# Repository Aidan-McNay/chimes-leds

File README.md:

# chimes-leds
A system for controlling McGraw Tower's clock face LEDs

## Documentation

Documentation for our system is located [here](https://aidan-mcnay.github.io/chimes-leds/)

Our documentation is built using Sphinx, and is
formatted as [reStructured Text](https://www.sphinx-doc.org/en/master/usage/restructuredtext/basics.html).
To build the documentation locally, first install Sphinx,
as well as our additional Sphinx modules:

```bash
pip install sphinx sphinx_rtd_theme sphinxcontrib-youtube
```

Then, you can build the output files in a `build`
directory with Sphinx, with the top-level HTML
located at `build/index.html`

```bash
sphinx-build docs build
```

This process is automated to update the Github page
on a push

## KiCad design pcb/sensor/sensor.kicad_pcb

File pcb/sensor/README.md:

# sensor

The PCB files for the control board at the playing stand level

## GPIO Mapping

**Microphone**:
 - **26**: Microphone ADC input

**Ambient Light**:
 - **21**: SCL
 - **20**: SDA
 - **19**: Interrupt (if desired)

**CAN connections**:
 - **16**: CAN TX
 - **17**: CAN RX
 - **22**: CAN Enable (active low)

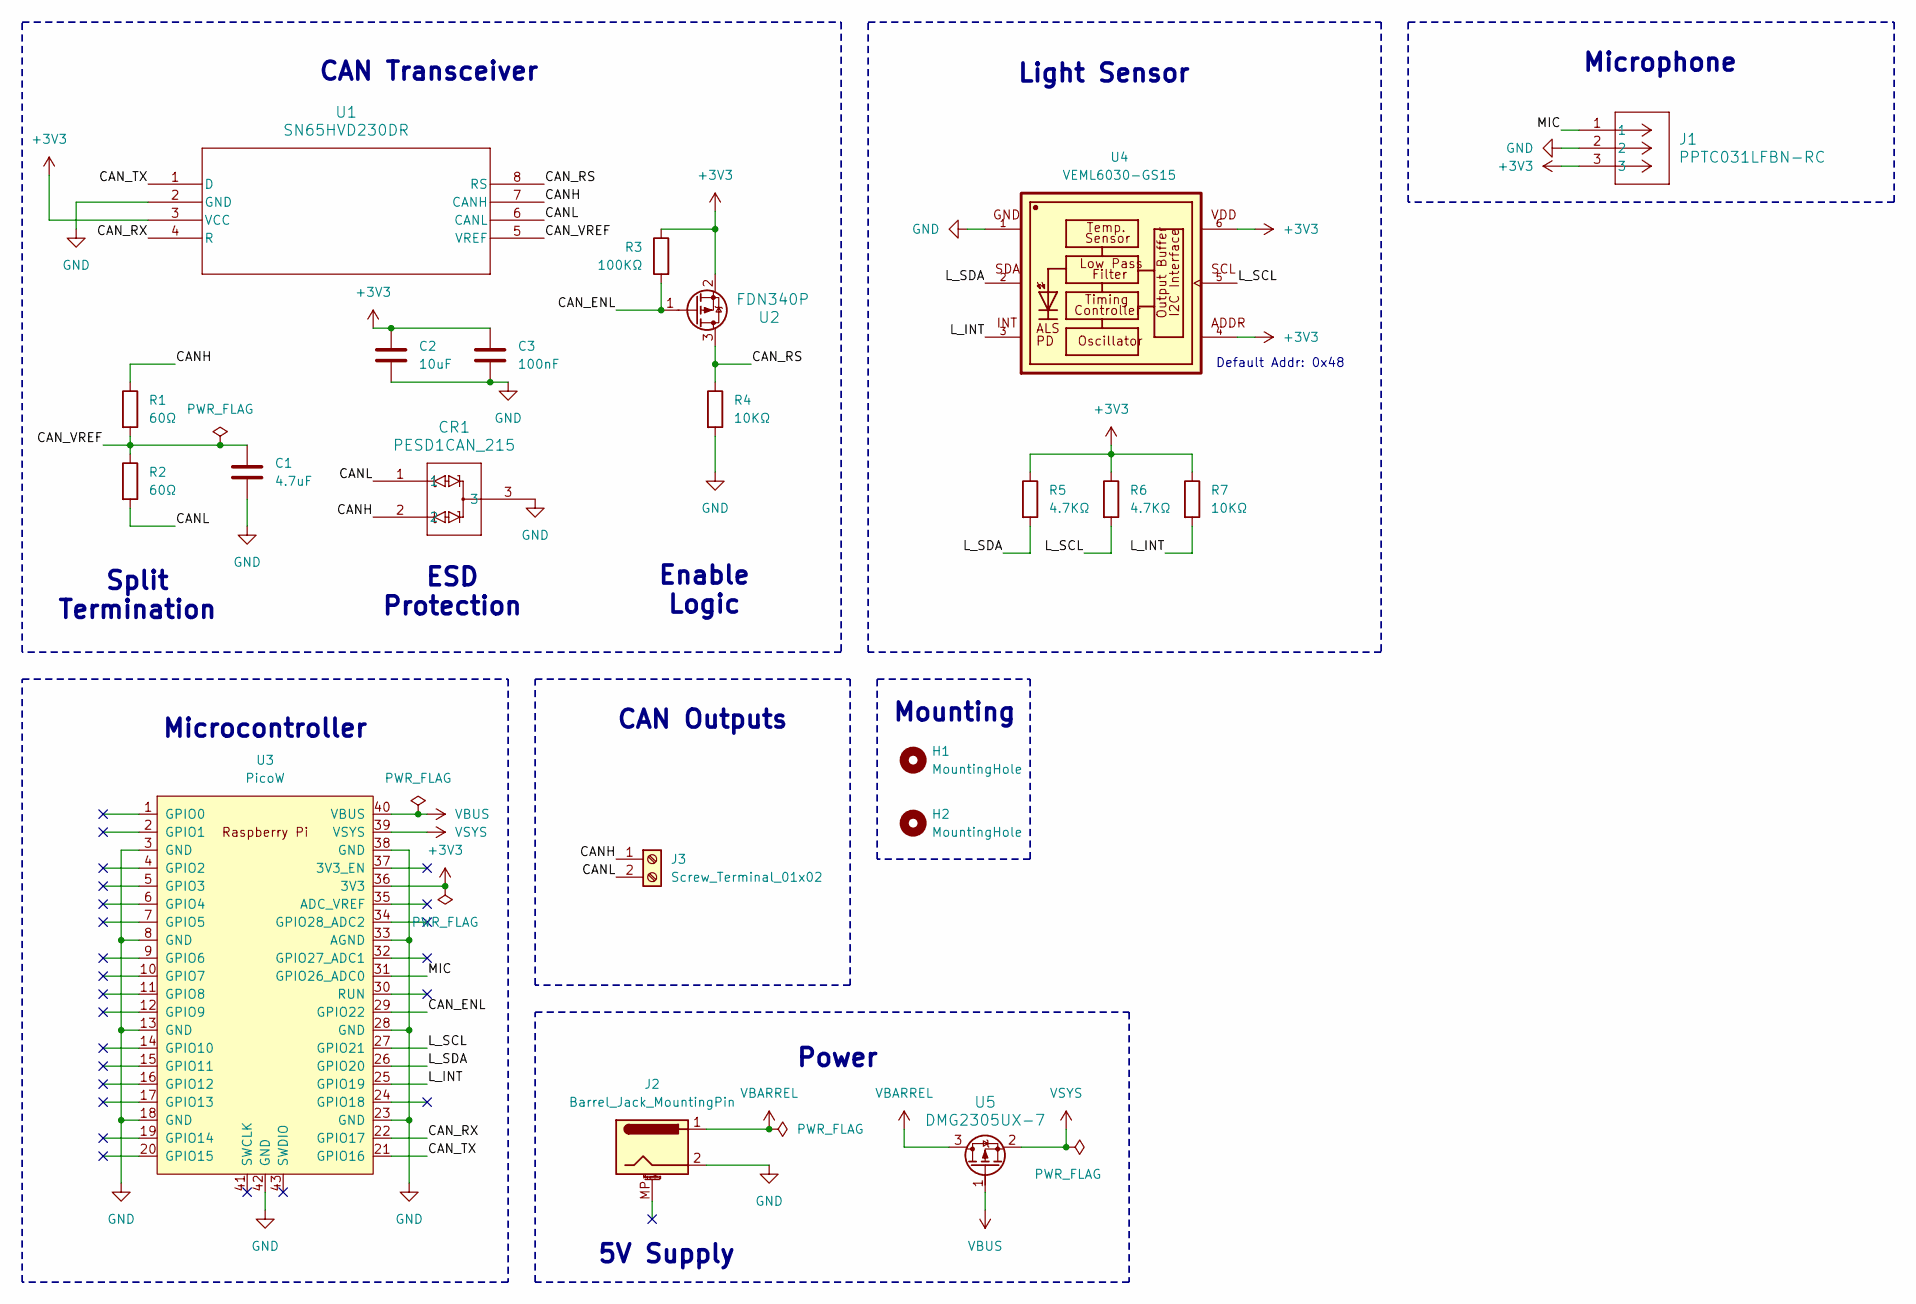
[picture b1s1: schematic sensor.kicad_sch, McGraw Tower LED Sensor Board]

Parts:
C1: 4.7uF; C_0603_1608Metric
C2: 10uF; C_0603_1608Metric
C3: 100nF; C_0603_1608Metric
CR1: PESD1CAN_215; SOT23_PESD1_NEX
H1, H2: MountingHole; MountingHole_3.2mm_M3_DIN965_Pad
J1: PPTC031LFBN-RC; CONN_PPTC031_SUL
J2: Barrel_Jack_MountingPin; BarrelJack_CUI_PJ-102AH_Horizontal
J3: Screw_Terminal_01x02; TerminalBlock_Phoenix_PT-1,5-2-5.0-H_1x02_P5.00mm_Horizontal
R1, R2: 60Ω; R_1206_3216Metric
R3: 100KΩ; R_0603_1608Metric
R4, R7: 10KΩ; R_0603_1608Metric
R5, R6: 4.7KΩ; R_0603_1608Metric
U1: SN65HVD230DR; D8
U2: FDN340P; SOT-23_ONS
U3: PicoW; RPi_PicoW_SMD_TH
U4: VEML6030-GS15; VISHAY_VEML6030_2X2X0.87
U5: DMG2305UX-7; SOT-23_DIO

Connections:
+3V3: C2.1, C3.1, J1.3, R3.1, R5.1, R6.1, R7.1, U1.3 (VCC), U2.2, U3.36 (3V3), U4.4, U4.6
/CANH: CR1.2, J3.1, R1.1, U1.7 (CANH)
/CANL: CR1.1, J3.2, R2.2, U1.6 (CANL)
/CAN_ENL: R3.2, U2.1, U3.29 (GPIO22)
/CAN_RS: R4.1, U1.8 (RS), U2.3
/CAN_RX: U1.4 (R), U3.22 (GPIO17)
/CAN_TX: U1.1 (D), U3.21 (GPIO16)
/CAN_VREF: C1.1, R1.2, R2.1, U1.5 (VREF)
/L_INT: R7.2, U3.25 (GPIO19), U4.3
/L_SCL: R6.2, U3.27 (GPIO21), U4.5
/L_SDA: R5.2, U3.26 (GPIO20), U4.2
/MIC: J1.1, U3.31 (GPIO26_ADC0)
GND: C1.2, C2.2, C3.2, CR1.3, J1.2, J2.2, R4.2, U1.2 (GND), U3.3 (GND), U3.8 (GND), U3.13 (GND), U3.18 (GND), U3.23 (GND), U3.28 (GND), U3.33 (AGND), U3.38 (GND), U3.42 (GND), U4.1
VBARREL: J2.1, U5.3
VBUS: U3.40 (VBUS), U5.1
VSYS: U3.39 (VSYS), U5.2

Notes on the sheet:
Microphone
CAN Outputs
Microcontroller
CAN Transceiver
Enable Logic
Power
5V Supply
Light Sensor
Mounting
ESD Protection
Split Termination
Default Addr: 0x48

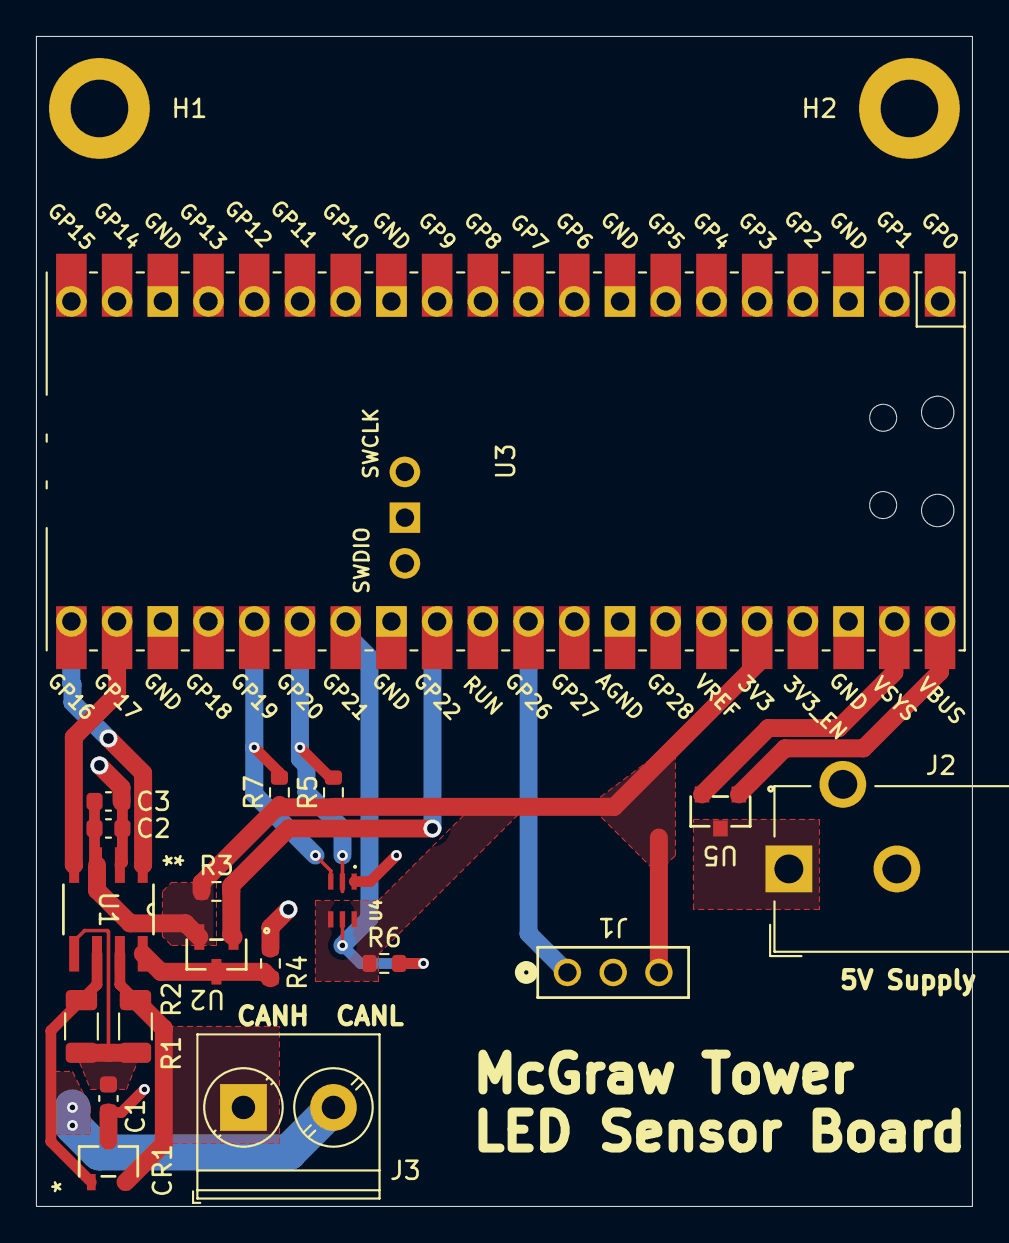
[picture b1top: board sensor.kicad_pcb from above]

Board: 2 copper layers, 52.0 x 65.0 mm, 21 parts (0 on the bottom side), 16 nets.

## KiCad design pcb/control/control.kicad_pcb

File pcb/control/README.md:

# control

The PCB files for the control board at the playing stand level

## GPIO Mapping

**System Configuration**:
 - **4**: System enable (whether to be on)
 - **5**: WiFi enable (whether to use WiFi configs)

**User Mode**:
 - **7**: "Light" mode (based on ambient light, set as pull-down)
 - **8**: "Music" mode (pulse with music, set as pull-down)
 - **9**: "On" mode (always on, set as pull-down)

**Color Potentiometer Inputs**
 - **28**: Red Potentiometer
 - **27**: Green Potentiometer
 - **26**: Blue Potentiometer

**Status LEDs**:
 - **10**: "On" LED (high when enabled)
 - **11**: Red LED (PWM for current color)
 - **12**: Green LED (PWM for current color)
 - **14**: Blue LED (PWM for current color)
 - **15**: WiFi LED (indicate where configs are from)

**Communication LEDs** *(whether we're communicating with a board)*:
 - **3**: Sensor Board
 - **21**: North Face
 - **20**: South Face
 - **19**: East Face
 - **18**: West Face

**CAN connections**:
 - **16**: CAN TX
 - **17**: CAN RX
 - **22**: CAN Enable (active low)

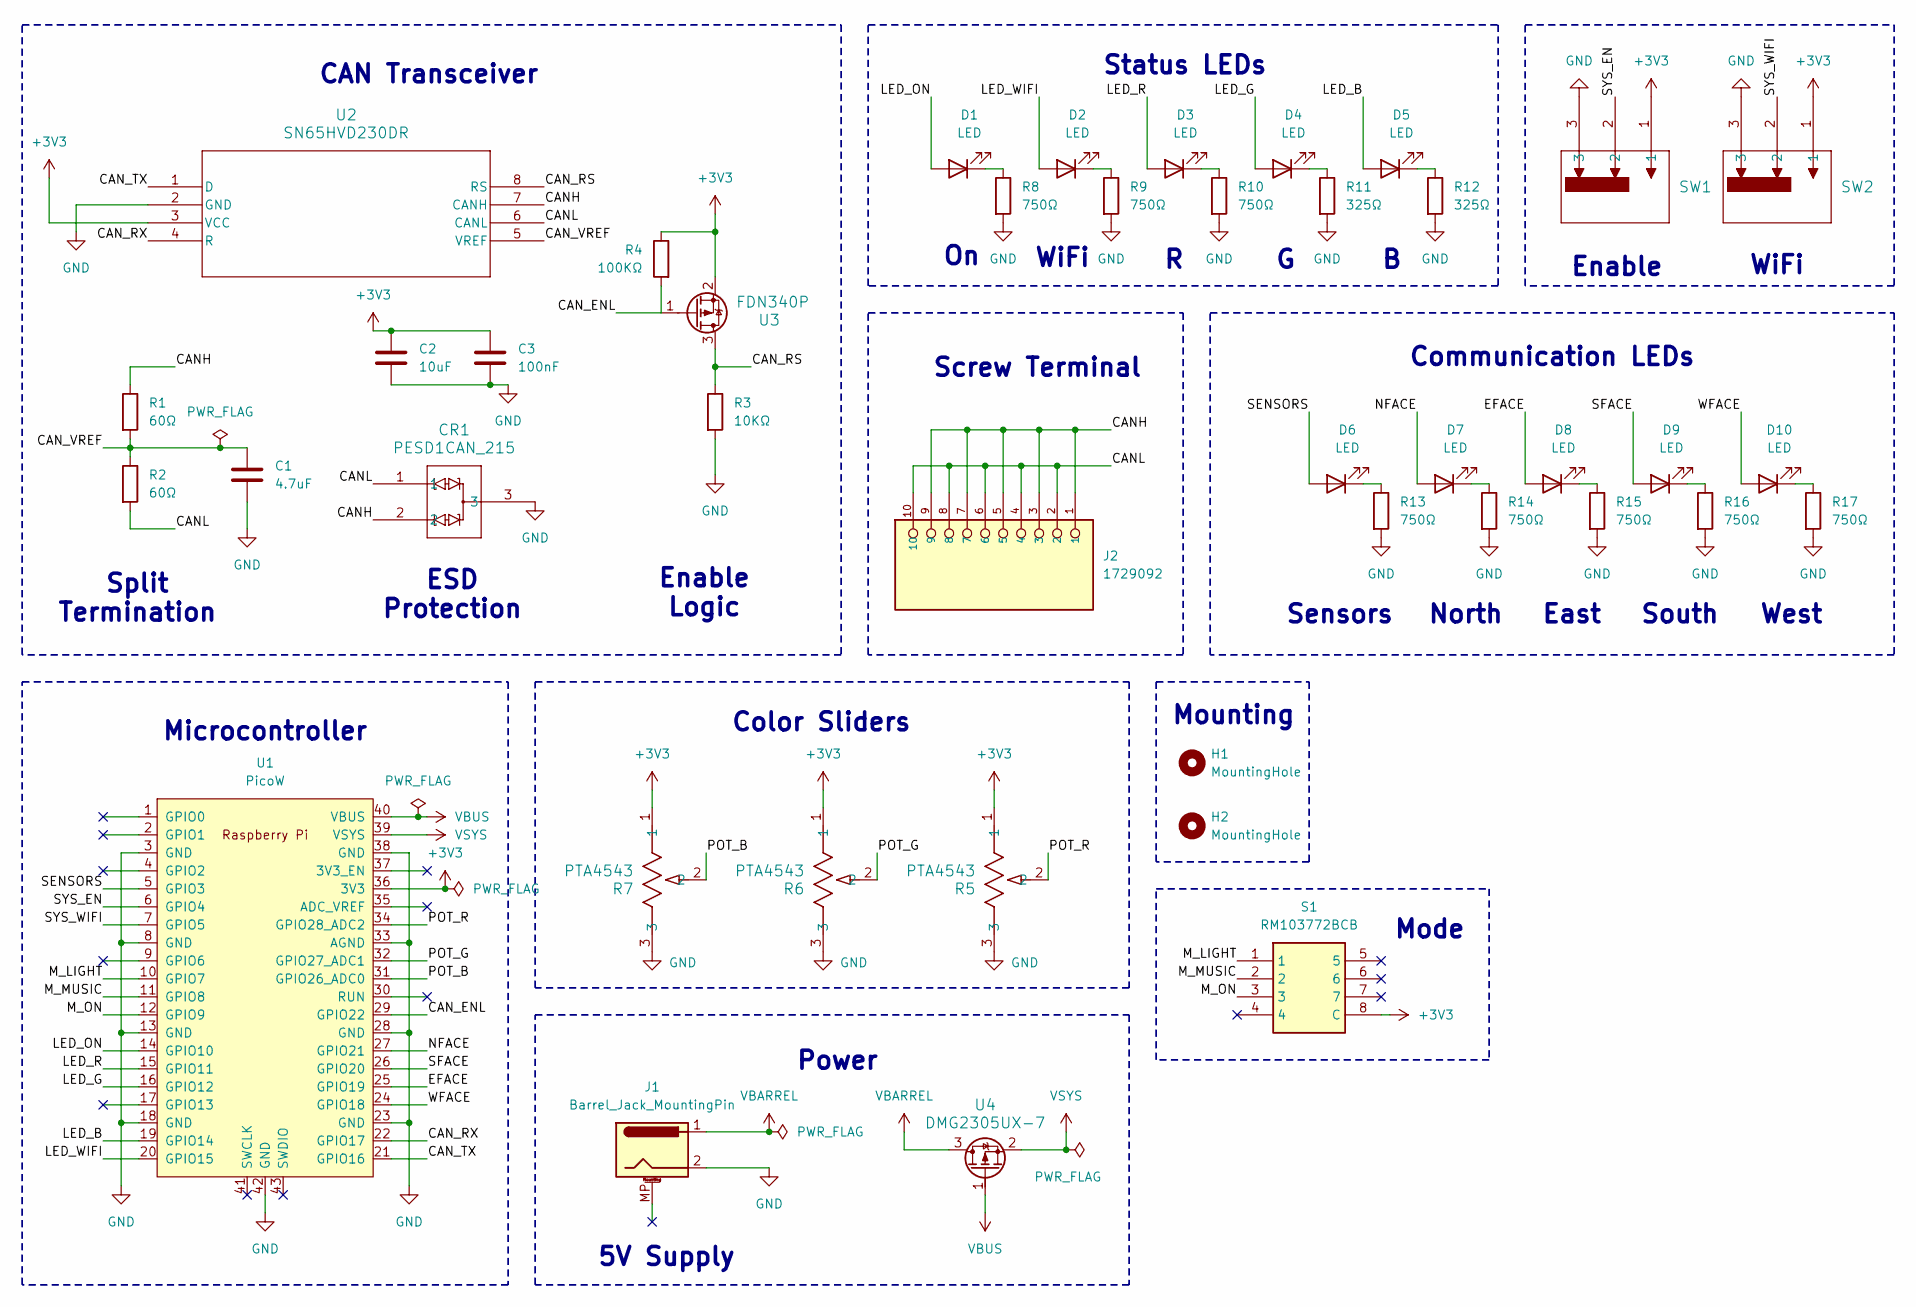
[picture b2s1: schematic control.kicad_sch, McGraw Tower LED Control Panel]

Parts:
C1: 4.7uF; C_0603_1608Metric
C2: 10uF; C_0603_1608Metric
C3: 100nF; C_0603_1608Metric
CR1: PESD1CAN_215; SOT23_PESD1_NEX
D1, D2, D3, D4, D5, D6, D7, D8, D9, D10: LED; LED_0603_1608Metric
H1, H2: MountingHole; MountingHole_3.2mm_M3_DIN965_Pad
J1: Barrel_Jack_MountingPin; BarrelJack_CUI_PJ-102AH_Horizontal
J2: 1729092; PHOENIX_1729092; DigiKey_Part_Number 277-1244-ND
R1, R2: 60Ω; R_1206_3216Metric
R3: 10KΩ; R_0603_1608Metric
R4: 100KΩ; R_0603_1608Metric
R5, R6, R7: PTA4543; POT_PTA4543
R8, R9, R10, R13, R14, R15, R16, R17: 750Ω; R_1206_3216Metric
R11, R12: 325Ω; R_0603_1608Metric
S1: RM103772BCB; Mouser Part Number 611-RM103772BCB
SW1, SW2: OS102011MS2QN1; SPDT_OS102011_CNK
U1: PicoW; RPi_PicoW_SMD_TH
U2: SN65HVD230DR; D8
U3: FDN340P; SOT-23_ONS
U4: DMG2305UX-7; SOT-23_DIO

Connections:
+3V3: C2.1, C3.1, R4.1, R5.1, R6.1, R7.1, S1.8 (C), SW1.1, SW2.1, U1.36 (3V3), U2.3 (VCC), U3.2
/CANH: CR1.2, J2.1, J2.3, J2.5, J2.7, J2.9, R1.1, U2.7 (CANH)
/CANL: CR1.1, J2.2, J2.4, J2.6, J2.8, J2.10, R2.2, U2.6 (CANL)
/CAN_ENL: R4.2, U1.29 (GPIO22), U3.1
/CAN_RS: R3.1, U2.8 (RS), U3.3
/CAN_RX: U1.22 (GPIO17), U2.4 (R)
/CAN_TX: U1.21 (GPIO16), U2.1 (D)
/CAN_VREF: C1.1, R1.2, R2.1, U2.5 (VREF)
/EFACE: D8.2 (A), U1.25 (GPIO19)
/LED_B: D5.2 (A), U1.19 (GPIO14)
/LED_G: D4.2 (A), U1.16 (GPIO12)
/LED_ON: D1.2 (A), U1.14 (GPIO10)
/LED_R: D3.2 (A), U1.15 (GPIO11)
/LED_WIFI: D2.2 (A), U1.20 (GPIO15)
/M_LIGHT: S1.1, U1.10 (GPIO7)
/M_MUSIC: S1.2, U1.11 (GPIO8)
/M_ON: S1.3, U1.12 (GPIO9)
/NFACE: D7.2 (A), U1.27 (GPIO21)
/POT_B: R7.2, U1.31 (GPIO26_ADC0)
/POT_G: R6.2, U1.32 (GPIO27_ADC1)
/POT_R: R5.2, U1.34 (GPIO28_ADC2)
/SENSORS: D6.2 (A), U1.5 (GPIO3)
/SFACE: D9.2 (A), U1.26 (GPIO20)
/SYS_EN: SW1.2, U1.6 (GPIO4)
/SYS_WIFI: SW2.2, U1.7 (GPIO5)
/WFACE: D10.2 (A), U1.24 (GPIO18)
GND: C1.2, C2.2, C3.2, CR1.3, J1.2, R3.2, R5.3, R6.3, R7.3, R8.2, R9.2, R10.2, R11.2, R12.2, R13.2, R14.2, R15.2, R16.2, R17.2, SW1.3, SW2.3, U1.3 (GND), U1.8 (GND), U1.13 (GND), U1.18 (GND), U1.23 (GND), U1.28 (GND), U1.33 (AGND), U1.38 (GND), U1.42 (GND), U2.2 (GND)
unnamed: D1.1 (K), R8.1
unnamed: D2.1 (K), R9.1
unnamed: D3.1 (K), R10.1
unnamed: D4.1 (K), R11.1
unnamed: D5.1 (K), R12.1
unnamed: D6.1 (K), R13.1
unnamed: D7.1 (K), R14.1
unnamed: D8.1 (K), R15.1
unnamed: D9.1 (K), R16.1
unnamed: D10.1 (K), R17.1
VBARREL: J1.1, U4.3
VBUS: U1.40 (VBUS), U4.1
VSYS: U1.39 (VSYS), U4.2

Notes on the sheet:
WiFi
Sensors
Status LEDs
5V Supply
Split Termination
Power
Mode
South
Color Sliders
Communication LEDs
Enable Logic
East
Enable
Screw Terminal
Microcontroller
CAN Transceiver
ESD Protection
North
Mounting
West

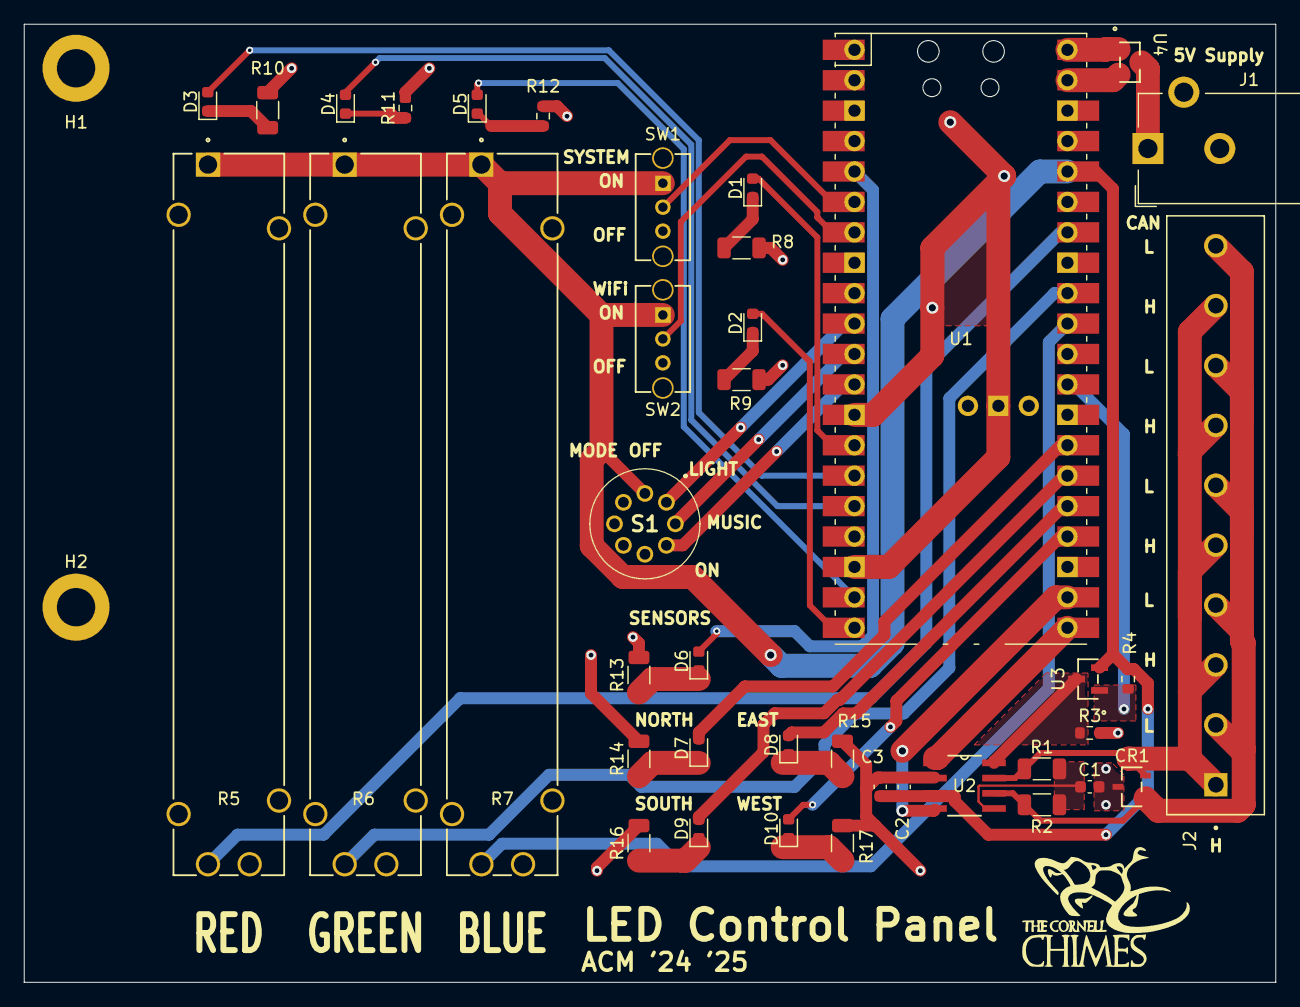
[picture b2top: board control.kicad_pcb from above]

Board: 2 copper layers, 104.5 x 80.0 mm, 42 parts (0 on the bottom side), 40 nets.

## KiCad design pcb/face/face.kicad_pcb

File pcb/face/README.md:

# face

The PCB files for the control board at the playing stand level

## GPIO Mapping

**LED PWM GPIOs (high for on)**:
 - **28**: Red LED
 - **26**: Green LED
 - **20**: Blue LED
 - **18**: White LED

**Status LEDs**:
 - **21**: "On" LED (high when enabled)
 - **19**: Communication LED (On when connected to control panel)

**CAN connections**:
 - **16**: CAN TX
 - **17**: CAN RX
 - **22**: CAN Enable (active low)

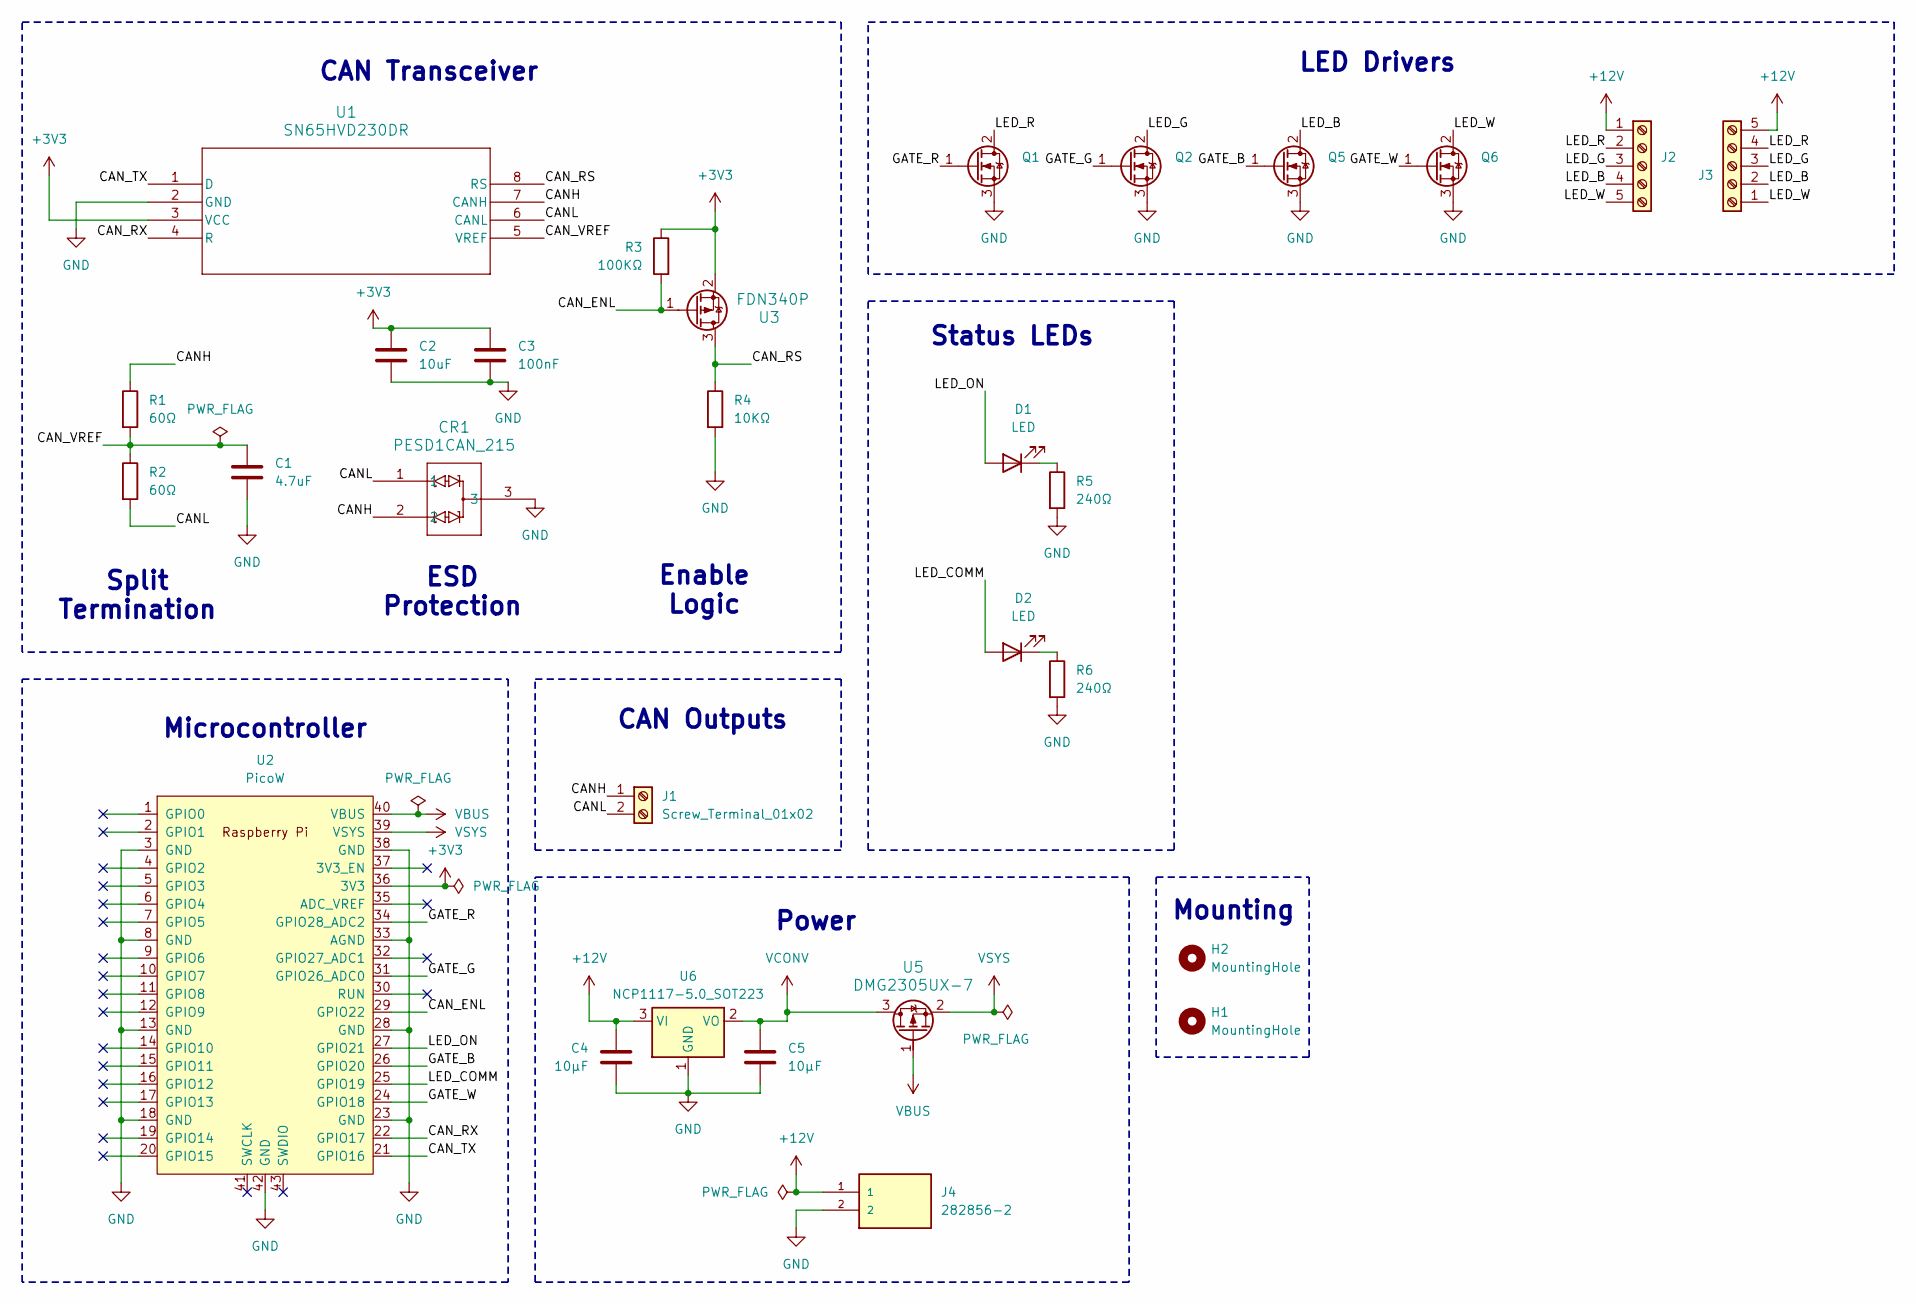
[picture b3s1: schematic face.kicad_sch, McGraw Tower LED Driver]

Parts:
C1: 4.7uF; C_0603_1608Metric
C2: 10uF; C_0603_1608Metric
C3: 100nF; C_0603_1608Metric
C4, C5: 10μF; C_0603_1608Metric
CR1: PESD1CAN_215; SOT23_PESD1_NEX
D1, D2: LED; LED_D5.0mm
H1, H2: MountingHole; MountingHole_3.2mm_M3_DIN965_Pad
J1: Screw_Terminal_01x02; TerminalBlock_Phoenix_PT-1,5-2-5.0-H_1x02_P5.00mm_Horizontal
J2, J3: Screw_Terminal_01x05; TerminalBlock_Phoenix_PT-1,5-5-5.0-H_1x05_P5.00mm_Horizontal
J4: 282856-2; TE_282856-2; PARTREV R
Q1, Q2, Q5, Q6: IRLB8721PBF; TO-220-3_Vertical
R1, R2: 60Ω; R_1206_3216Metric
R3: 100KΩ; R_0603_1608Metric
R4: 10KΩ; R_0603_1608Metric
R5, R6: 240Ω; R_0603_1608Metric
U1: SN65HVD230DR; D8
U2: PicoW; RPi_PicoW_SMD_TH
U3: FDN340P; SOT-23_ONS
U5: DMG2305UX-7; SOT-23_DIO
U6: NCP1117-5.0_SOT223; SOT-223-3_TabPin2

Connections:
+3V3: C2.1, C3.1, R3.1, U1.3 (VCC), U2.36 (3V3), U3.2
+12V: C4.1, J2.1, J3.5, J4.1, U6.3 (VI)
/CANH: CR1.2, J1.1, R1.1, U1.7 (CANH)
/CANL: CR1.1, J1.2, R2.2, U1.6 (CANL)
/CAN_ENL: R3.2, U2.29 (GPIO22), U3.1
/CAN_RS: R4.1, U1.8 (RS), U3.3
/CAN_RX: U1.4 (R), U2.22 (GPIO17)
/CAN_TX: U1.1 (D), U2.21 (GPIO16)
/CAN_VREF: C1.1, R1.2, R2.1, U1.5 (VREF)
/GATE_B: Q5.1 (G), U2.26 (GPIO20)
/GATE_G: Q2.1 (G), U2.31 (GPIO26_ADC0)
/GATE_R: Q1.1 (G), U2.34 (GPIO28_ADC2)
/GATE_W: Q6.1 (G), U2.24 (GPIO18)
/LED_B: J2.4, J3.2, Q5.2 (D)
/LED_COMM: D2.2 (A), U2.25 (GPIO19)
/LED_G: J2.3, J3.3, Q2.2 (D)
/LED_ON: D1.2 (A), U2.27 (GPIO21)
/LED_R: J2.2, J3.4, Q1.2 (D)
/LED_W: J2.5, J3.1, Q6.2 (D)
GND: C1.2, C2.2, C3.2, C4.2, C5.2, CR1.3, J4.2, Q1.3 (S), Q2.3 (S), Q5.3 (S), Q6.3 (S), R4.2, R5.2, R6.2, U1.2 (GND), U2.3 (GND), U2.8 (GND), U2.13 (GND), U2.18 (GND), U2.23 (GND), U2.28 (GND), U2.33 (AGND), U2.38 (GND), U2.42 (GND), U6.1 (GND)
unnamed: D1.1 (K), R5.1
unnamed: D2.1 (K), R6.1
VBUS: U2.40 (VBUS), U5.1
VCONV: C5.1, U5.3, U6.2 (VO)
VSYS: U2.39 (VSYS), U5.2

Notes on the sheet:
LED Drivers
Status LEDs
Microcontroller
CAN Transceiver
Mounting
CAN Outputs
Enable Logic
Split Termination
ESD Protection
Power

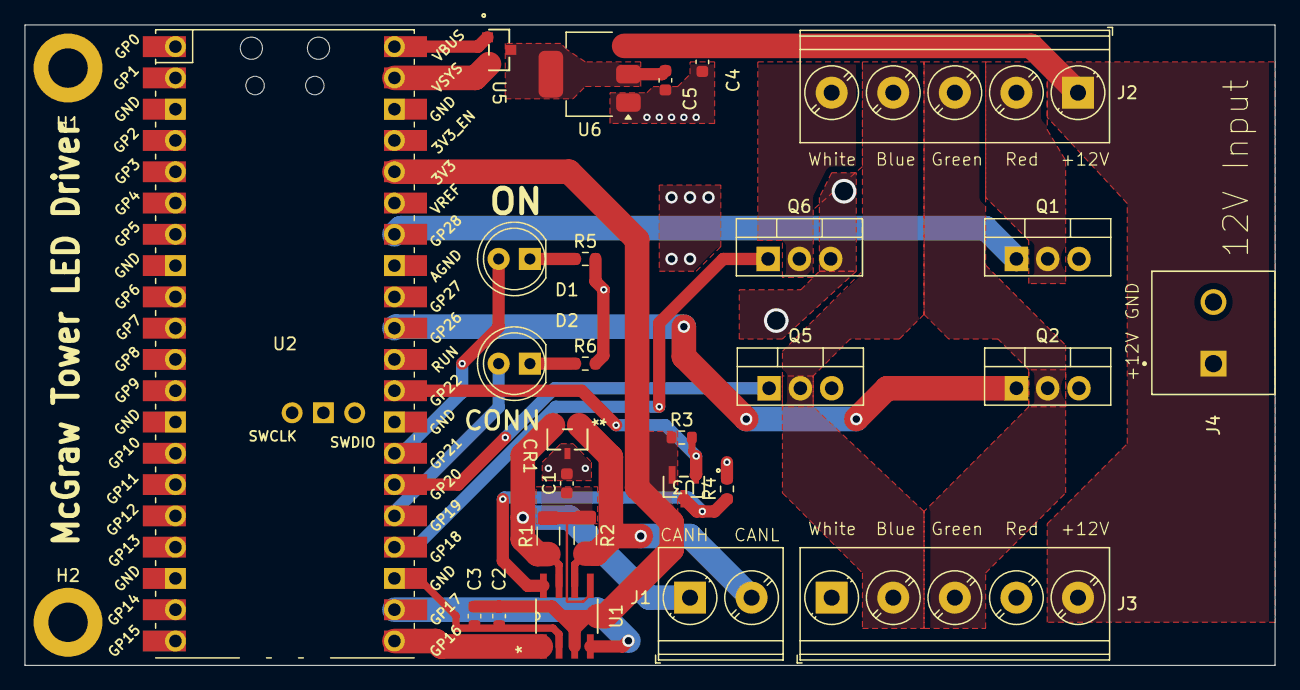
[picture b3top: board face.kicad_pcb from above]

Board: 2 copper layers, 101.5 x 52.0 mm, 29 parts (0 on the bottom side), 25 nets.

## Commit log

2025-04-08 Initial port
2025-04-08 Remove extra files
2025-04-08 Revise CMake
2025-04-08 Started control PCB
2025-04-08 Remove KiCad backups
2025-04-08 Update gitignore
2025-04-08 Remove external libs
2025-04-09 Working on control PCB more
2025-04-09 Rename readme
2025-04-09 Schematic finished, working on layout
2025-04-09 Update control schematic
2025-04-09 Control PCB done
2025-04-09 Increase power trace width
2025-04-10 Started sensor board
2025-04-10 Add light sensor
2025-04-14 Worked on PCBs
2025-04-14 transfer
2025-04-14 Incremental PCB
2025-04-14 We love CMake
2025-04-14 CAN with shorts
2025-04-14 core skeleton
2025-04-18 PCBs hopefully done
2025-04-19 Final boards
2025-04-20 core
2025-04-21 Pin mapping
2025-04-21 clock face core
2025-04-23 working calibration script
2025-04-24 Update CAN based on CAN interface
2025-04-24 Update CAN based on interface
2025-04-28 multicore
2025-04-28 fixed calibration software
2025-04-28 Start website
2025-04-28 Include permissions
2025-05-02 working adc round robin
2025-05-02 reimplement CAN bus
2025-05-02 final update
2025-05-03 cleanup CAN code
2025-05-04 small cleanups
2025-05-04 test
2025-05-04 WORKING TX
2025-05-08 Intro
2025-05-08 working
2025-05-08 Start working on HW design
2025-05-08 deploy: 5572aafcb8ea63c1f2b50318e6b835b52988769d
2025-05-14 Include automatic source file inclusion
2025-05-14 Updated appendices
2025-05-14 Include favicon
2025-05-14 Appendix syntax
2025-05-14 Update appendices
2025-05-14 Add references
2025-05-14 final version
2025-05-14 cleanup
2025-05-14 HW Description done except for pics
2025-05-14 CAN Transceiver details
2025-05-14 Explain acronym
2025-05-14 start working on program description
2025-05-14 control board
2025-05-14 sensor board
2025-05-14 Wrote Conclusions Part
2025-05-15 Termination
2025-05-15 Add video
2025-05-15 High-Level
2025-05-15 Update conclusion
2025-05-15 Results
2025-05-15 finish program design
2025-05-16 deploy: f4092670529b8a6b6dd58e5be656a6fc4583fedf
